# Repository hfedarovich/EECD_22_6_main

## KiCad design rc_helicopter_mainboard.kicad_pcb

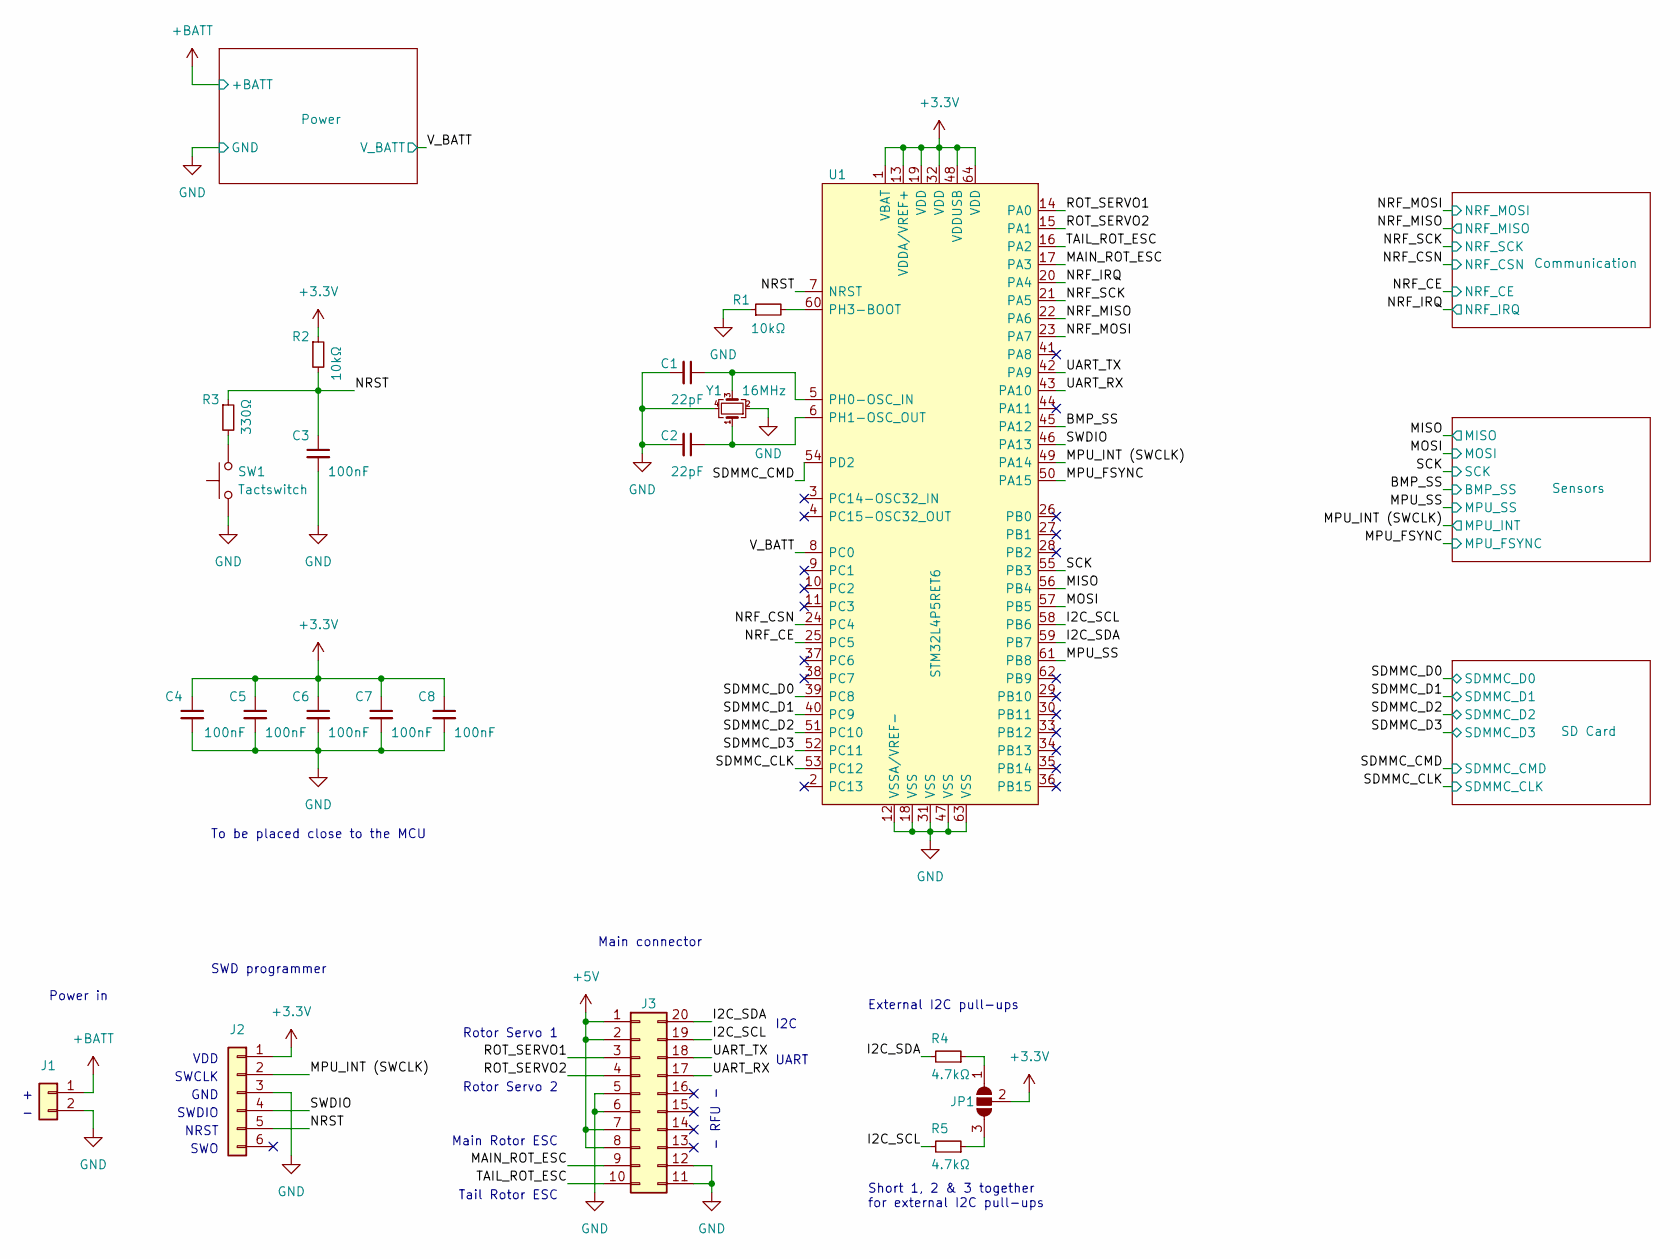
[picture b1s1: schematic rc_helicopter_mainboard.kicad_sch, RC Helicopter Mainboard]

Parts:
C1, C2: 22pF; C_0603_1608Metric
C3, C4, C5, C6, C7, C8: 100nF; C_0603_1608Metric
J1: Battery Pack; Molex_KK-254_AE-6410-02A_1x02_P2.54mm_Vertical
J2: SWD; PinHeader_2x03_P2.54mm_Vertical
J3: Main Connector; PinHeader_2x10_P2.54mm_Horizontal
JP1: SolderJumper_3_Open; SolderJumper-3_P1.3mm_Open_RoundedPad1.0x1.5mm_NumberLabels
R1, R2: 10kΩ; R_0603_1608Metric
R3: 330Ω; R_0603_1608Metric
R4, R5: 4.7kΩ; R_0603_1608Metric
SW1: Tactswitch; SW_SPST_PTS645
U1: STM32L4P5RET6; LQFP-64_10x10mm_P0.5mm
Y1: 16MHz; Crystal_SMD_3225-4Pin_3.2x2.5mm

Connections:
+3.3V: C4.1, C5.1, C6.1, C7.1, C8.1, J2.1, JP1.2 (C), R2.1, U1.1 (VBAT), U1.13 (VDDA/VREF+), U1.19 (VDD), U1.32 (VDD), U1.48 (VDDUSB), U1.64 (VDD); also elsewhere on the board
+5V: J3.1, J3.2, J3.7, J3.8; also elsewhere on the board
+BATT: J1.1; also elsewhere on the board
/BMP_SS: U1.45 (PA12); also elsewhere on the board
/I2C_SCL: J3.19, R5.2, U1.58 (PB6)
/I2C_SDA: J3.20, R4.2, U1.59 (PB7)
/MAIN_ROT_ESC: J3.9, U1.17 (PA3)
/MISO: U1.56 (PB4); also elsewhere on the board
/MOSI: U1.57 (PB5); also elsewhere on the board
/MPU_FSYNC: U1.50 (PA15); also elsewhere on the board
/MPU_INT (SWCLK): J2.2, U1.49 (PA14); also elsewhere on the board
/MPU_SS: U1.61 (PB8); also elsewhere on the board
/NRF_CE: U1.25 (PC5); also elsewhere on the board
/NRF_CSN: U1.24 (PC4); also elsewhere on the board
/NRF_IRQ: U1.20 (PA4); also elsewhere on the board
/NRF_MISO: U1.22 (PA6); also elsewhere on the board
/NRF_MOSI: U1.23 (PA7); also elsewhere on the board
/NRF_SCK: U1.21 (PA5); also elsewhere on the board
/NRST: C3.1, J2.5, R2.2, R3.1, U1.7 (NRST)
/ROT_SERVO1: J3.3, U1.14 (PA0)
/ROT_SERVO2: J3.4, U1.15 (PA1)
/SCK: U1.55 (PB3); also elsewhere on the board
/SDMMC_CLK: U1.53 (PC12); also elsewhere on the board
/SDMMC_CMD: U1.54 (PD2); also elsewhere on the board
/SDMMC_D0: U1.39 (PC8); also elsewhere on the board
/SDMMC_D1: U1.40 (PC9); also elsewhere on the board
/SDMMC_D2: U1.51 (PC10); also elsewhere on the board
/SDMMC_D3: U1.52 (PC11); also elsewhere on the board
/SWDIO: J2.4, U1.46 (PA13)
/TAIL_ROT_ESC: J3.10, U1.16 (PA2)
/UART_RX: J3.17, U1.43 (PA10)
/UART_TX: J3.18, U1.42 (PA9)
/V_BATT: U1.8 (PC0); also elsewhere on the board
GND: C1.2, C2.2, C3.2, C4.2, C5.2, C6.2, C7.2, C8.2, J1.2, J2.3, J3.5, J3.6, J3.11, J3.12, R1.1, SW1.1, U1.12 (VSSA/VREF-), U1.18 (VSS), U1.31 (VSS), U1.47 (VSS), U1.63 (VSS), Y1.2, Y1.4; also elsewhere on the board
unnamed: C1.1, U1.5 (PH0-OSC_IN), Y1.3
unnamed: C2.1, U1.6 (PH1-OSC_OUT), Y1.1
unnamed: JP1.1 (A), R4.1
unnamed: JP1.3 (B), R5.1
unnamed: R1.2, U1.60 (PH3-BOOT)
unnamed: R3.2, SW1.2

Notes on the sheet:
Tail Rotor ESC
Rotor Servo 1
- RFU -
SWDIO
SWO
NRST
SWCLK
External I2C pull-ups
VDD
To be placed close to the MCU
Main connector
Rotor Servo 2
Short 1, 2 & 3 together for external I2C pull-ups
Power in
SWD programmer
GND
Main Rotor ESC
I2C
UART

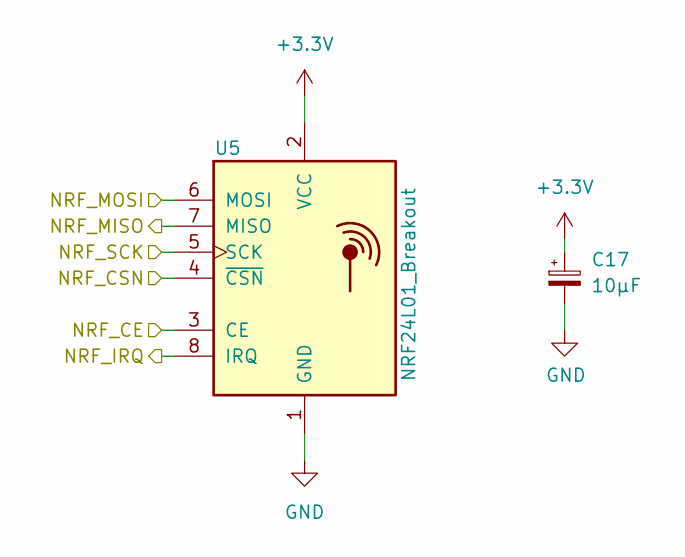
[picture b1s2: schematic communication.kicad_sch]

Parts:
C17: 10μF; CP_EIA-3216-10_Kemet-I
U5: NRF24L01_Breakout; nRF24L01_Breakout

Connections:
+3.3V: C17.1, U5.2 (VCC); also elsewhere on the board
/NRF_CE: U5.3 (CE); also elsewhere on the board
/NRF_CSN: U5.4 (~CSN); also elsewhere on the board
/NRF_IRQ: U5.8 (IRQ); also elsewhere on the board
/NRF_MISO: U5.7 (MISO); also elsewhere on the board
/NRF_MOSI: U5.6 (MOSI); also elsewhere on the board
/NRF_SCK: U5.5 (SCK); also elsewhere on the board
GND: C17.2, U5.1 (GND); also elsewhere on the board

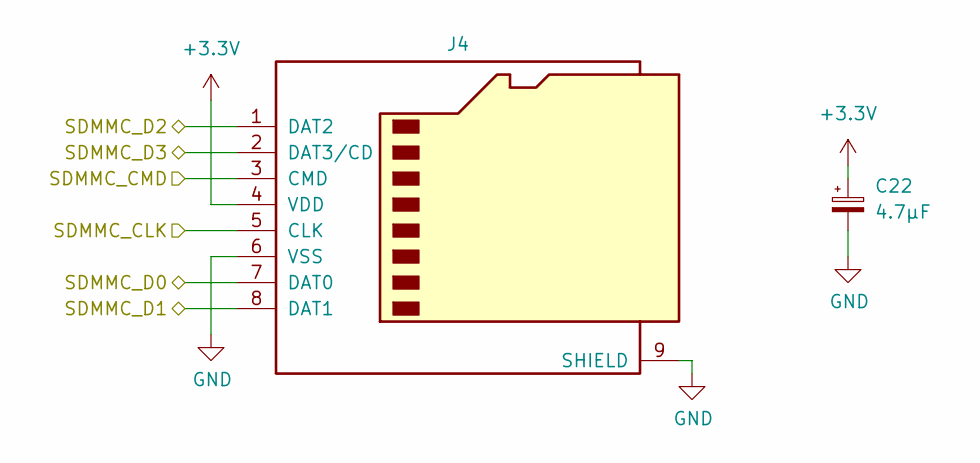
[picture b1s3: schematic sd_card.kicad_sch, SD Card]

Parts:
C22: 4.7μF; CP_EIA-3216-10_Kemet-I
J4: Micro_SD_Card; 112K-TAA0-RA1

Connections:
+3.3V: C22.1, J4.4 (VDD); also elsewhere on the board
/SDMMC_CLK: J4.5 (CLK); also elsewhere on the board
/SDMMC_CMD: J4.3 (CMD); also elsewhere on the board
/SDMMC_D0: J4.7 (DAT0); also elsewhere on the board
/SDMMC_D1: J4.8 (DAT1); also elsewhere on the board
/SDMMC_D2: J4.1 (DAT2); also elsewhere on the board
/SDMMC_D3: J4.2 (DAT3/CD); also elsewhere on the board
GND: C22.2, J4.6 (VSS), J4.9 (SHIELD); also elsewhere on the board

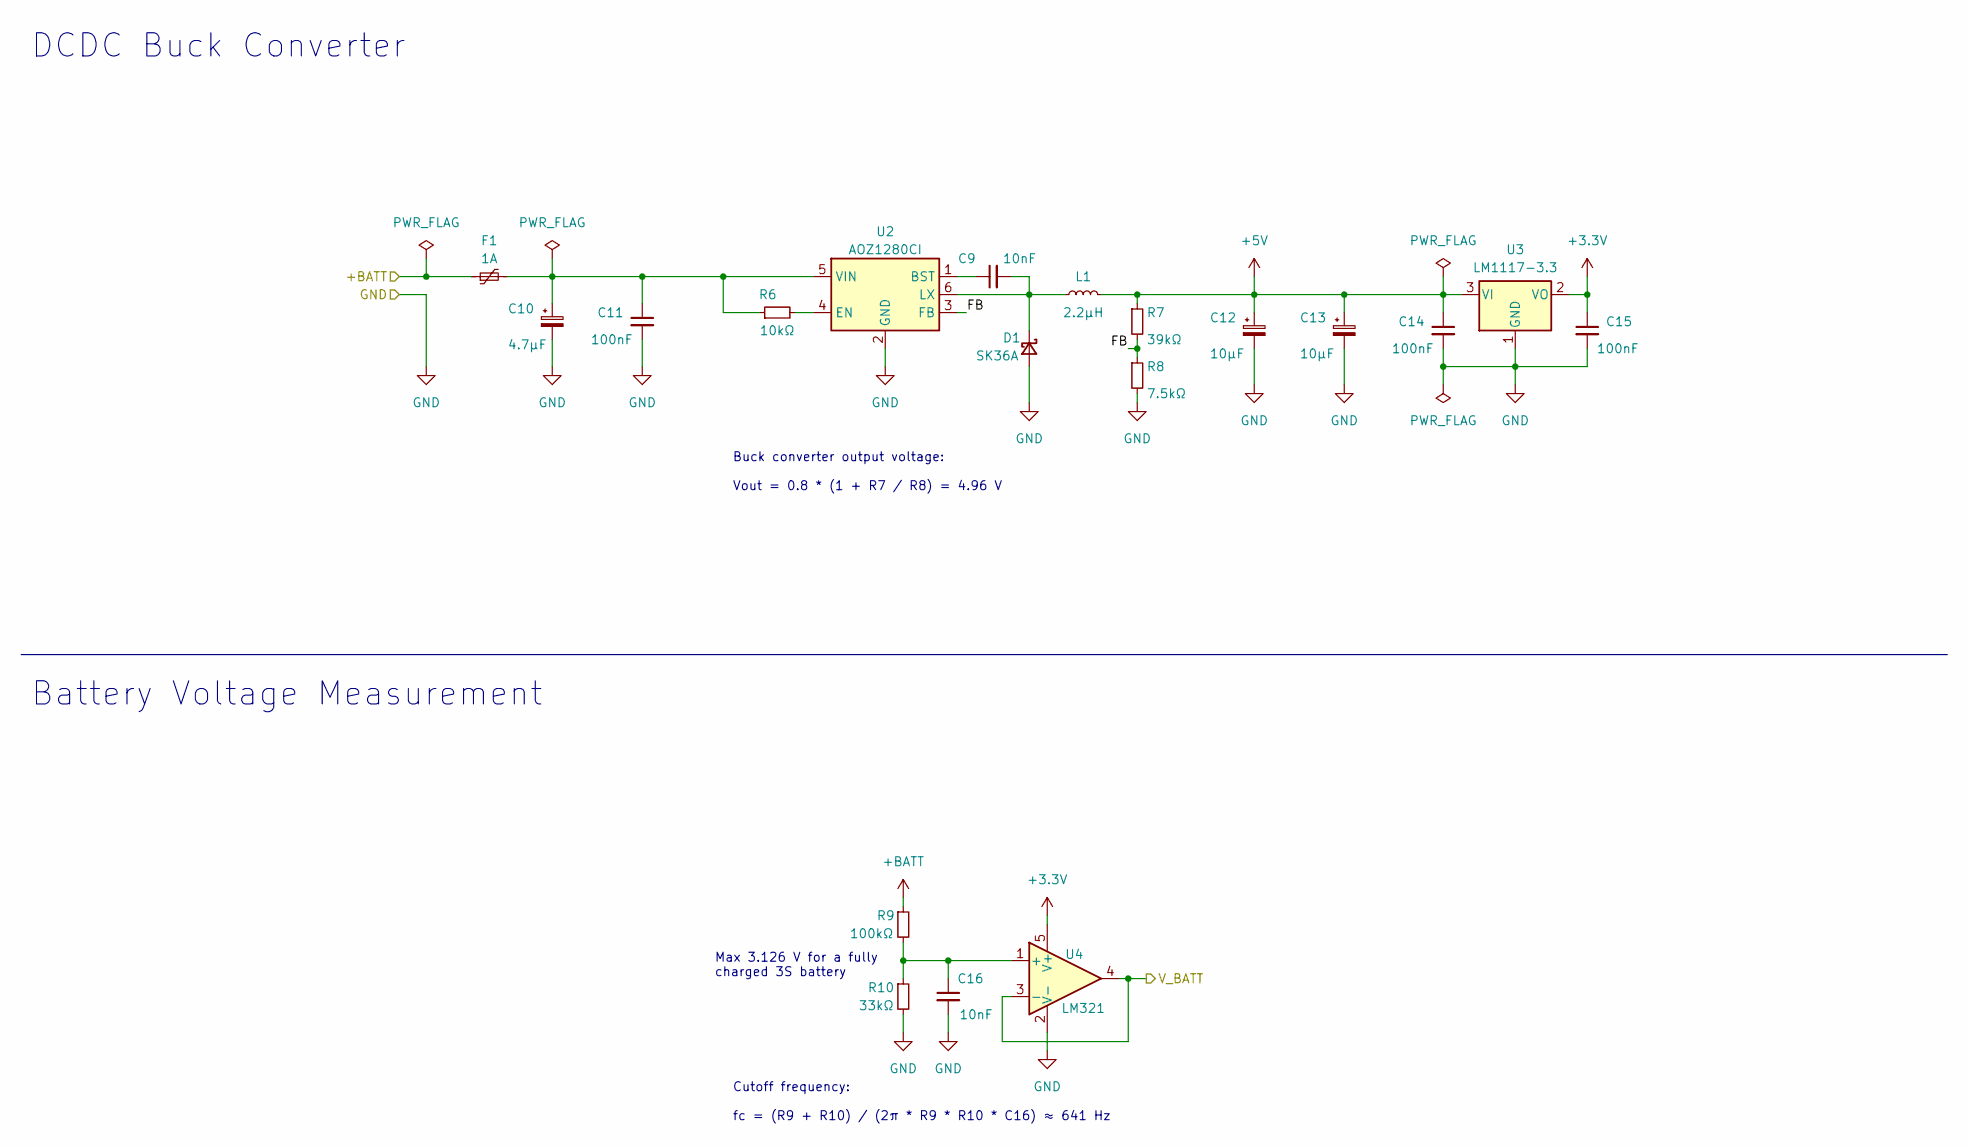
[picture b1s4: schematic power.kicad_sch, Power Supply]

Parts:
C9, C16: 10nF; C_0603_1608Metric
C10: 4.7μF; CP_Elec_6.3x5.4
C11, C14, C15: 100nF; C_0603_1608Metric
C12: 10μF; CP_Elec_6.3x5.4
C13: 10μF; CP_EIA-3216-10_Kemet-I
D1: SK36A; D_SMA
F1: 1A; Fuse_1210_3225Metric
L1: 2.2μH; L_Bourns-SRN4018
R6: 10kΩ; R_0603_1608Metric
R7: 39kΩ; R_0603_1608Metric
R8: 7.5kΩ; R_0603_1608Metric
R9: 100kΩ; R_0603_1608Metric
R10: 33kΩ; R_0603_1608Metric
U2: AOZ1280CI; SOT-23-6
U3: LM1117-3.3; SOT-223-3_TabPin2
U4: LM321; SOT-23-5

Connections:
+3.3V: C15.1, U3.2 (VO), U4.5 (V+); also elsewhere on the board
+5V: C12.1, C13.1, C14.1, L1.2, R7.1, U3.3 (VI); also elsewhere on the board
+BATT: F1.1, R9.1; also elsewhere on the board
/Power/FB: R7.2, R8.1, U2.3 (FB)
/V_BATT: U4.3 (-), U4.4; also elsewhere on the board
GND: C10.2, C11.2, C12.2, C13.2, C14.2, C15.2, C16.2, D1.2 (A), R8.2, R10.2, U2.2 (GND), U3.1 (GND), U4.2 (V-); also elsewhere on the board
unnamed: C9.1, U2.1 (BST)
unnamed: C9.2, D1.1 (K), L1.1, U2.6 (LX)
unnamed: C10.1, C11.1, F1.2, R6.1, U2.5 (VIN)
unnamed: C16.1, R9.2, R10.1, U4.1 (+)
unnamed: R6.2, U2.4 (EN)

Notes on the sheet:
Max 3.126 V for a fully charged 3S battery
Buck converter output voltage: Vout = 0.8 * (1 + R7 / R8) = 4.96 V
Battery Voltage Measurement
Cutoff frequency: fc = (R9 + R10) / (2π * R9 * R10 * C16) ≈ 641 Hz
DCDC Buck Converter

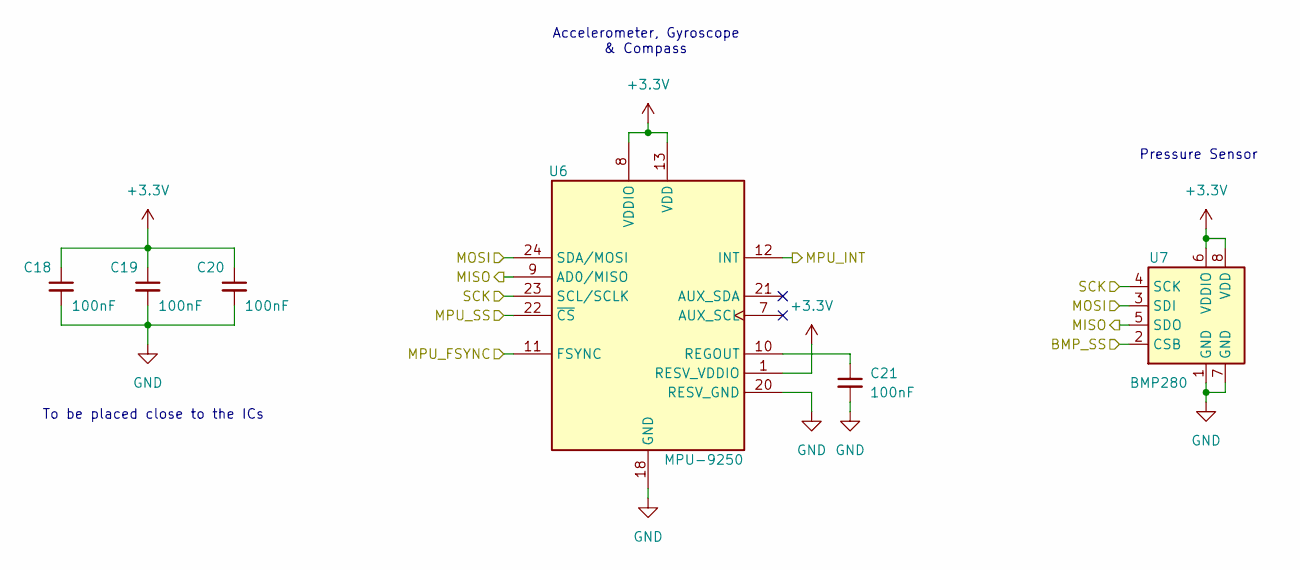
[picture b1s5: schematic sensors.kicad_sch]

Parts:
C18, C19, C20, C21: 100nF; C_0603_1608Metric
U6: MPU-9250; InvenSense_QFN-24_3x3mm_P0.4mm
U7: BMP280; Bosch_LGA-8_2x2.5mm_P0.65mm_ClockwisePinNumbering

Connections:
+3.3V: C18.1, C19.1, C20.1, U6.1 (RESV_VDDIO), U6.8 (VDDIO), U6.13 (VDD), U7.6 (VDDIO), U7.8 (VDD); also elsewhere on the board
/BMP_SS: U7.2 (CSB); also elsewhere on the board
/MISO: U6.9 (AD0/MISO), U7.5 (SDO); also elsewhere on the board
/MOSI: U6.24 (SDA/MOSI), U7.3 (SDI); also elsewhere on the board
/MPU_FSYNC: U6.11 (FSYNC); also elsewhere on the board
/MPU_INT (SWCLK): U6.12 (INT); also elsewhere on the board
/MPU_SS: U6.22 (~CS); also elsewhere on the board
/SCK: U6.23 (SCL/SCLK), U7.4 (SCK); also elsewhere on the board
GND: C18.2, C19.2, C20.2, C21.2, U6.18 (GND), U6.20 (RESV_GND), U7.1 (GND), U7.7 (GND); also elsewhere on the board
unnamed: C21.1, U6.10 (REGOUT)

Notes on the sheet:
Pressure Sensor
Accelerometer, Gyroscope & Compass
To be placed close to the ICs

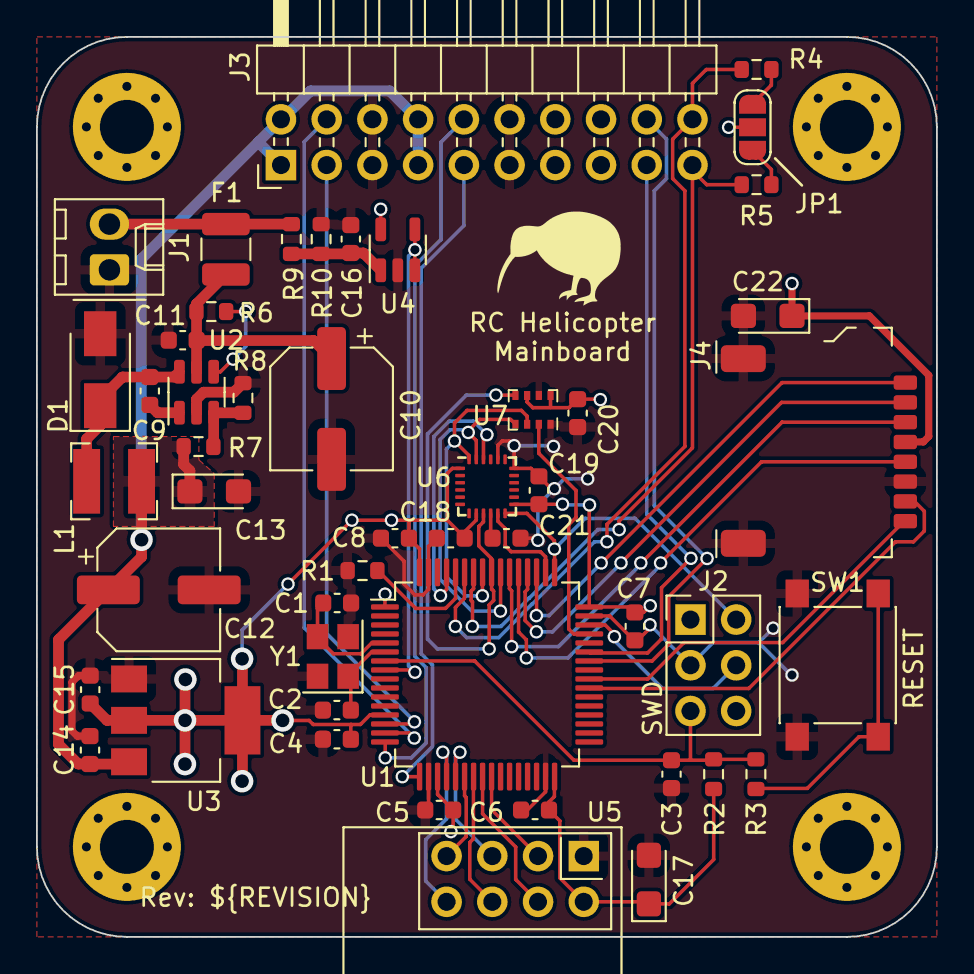
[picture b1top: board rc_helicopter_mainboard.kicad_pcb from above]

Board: 2 copper layers, 50.0 x 50.0 mm, 49 parts (0 on the bottom side), 47 nets.

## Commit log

2022-11-22 add functions for sd-card/ems/nrf24
2022-12-12 Refactor the mainboard
    - Use smaller STM
    - Use MPU-9250 as a motion sensor
    - Connect some peripherals to the MCU
2022-12-16 Connect sensors to the MCU
2022-12-16 Add local library
2022-12-17 Improve the power section:
    - add ADC circuit to measure battery level
    - add 5V LDO regulator
2022-12-17 Add external UART and I2C connectors
2022-12-17 Add project logo
2022-12-17 Assign footprints to symbols
2022-12-17 Rename the project
2022-12-22 Use single connector for I/O
2022-12-23 Remove 5V LDO regulator
2022-12-28 Arrange footprints
2022-12-28 Move symbols to a separate directory
2023-01-09 Rearrange footprints
2023-01-17 Route PCB tracks
2023-01-17 Release v1.0.0
